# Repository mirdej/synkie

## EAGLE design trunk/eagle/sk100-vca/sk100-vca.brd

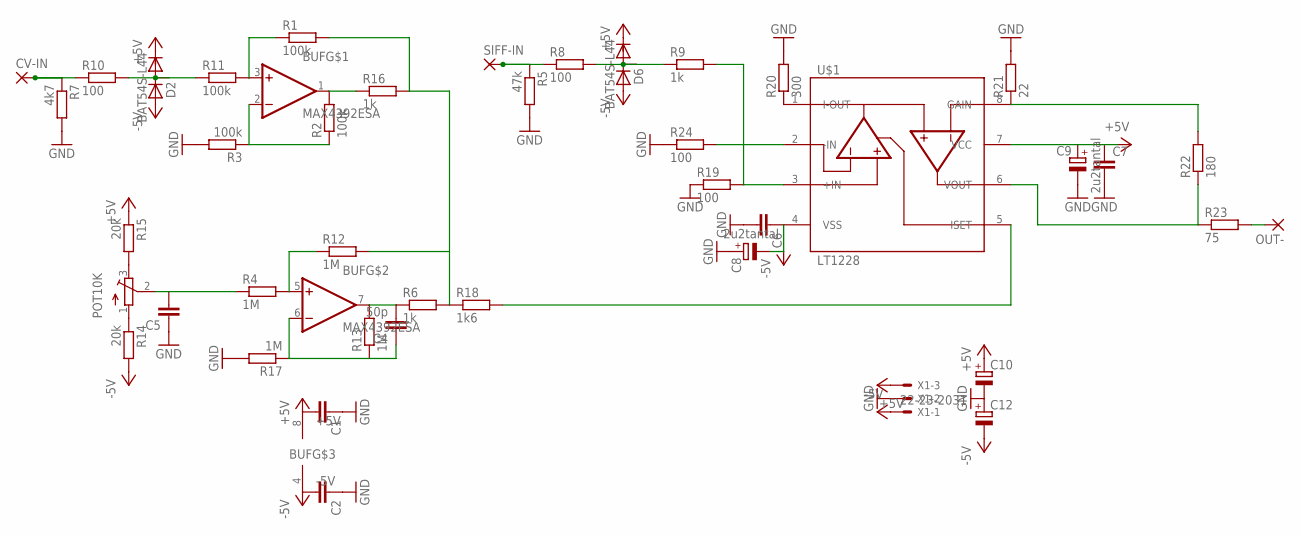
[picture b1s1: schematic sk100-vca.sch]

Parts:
BUF: MAX4392ESA; SO08
C1, C2, C5, C6, C7: C-EUC1206; C1206
C4: 50p; C1206
C8, C9: 2u2tantal; CT6032
C10, C12: CPOL-EUCT6032; CT6032
CV-IN: 3,17/1,1
D2, D6: BAT54S-L44; SOT23
OUT-: 3,17/1,1
POT10K: 10k; ALPS_RK09K111_H
R1, R2, R3, R11: 100k; R1206
R4, R12, R13, R17: 1M; R1206
R5: 47k; R1206
R6, R9, R16: 1k; R1206
R7: 4k7; R1206
R8, R10, R19, R24: 100; R1206
R14, R15: 20k; R1206
R18: 1k6; R1206
R20: 300; R1206
R21: 22; R1206
R22: 180; R1206
R23: 75; R1206
SIFF-IN: 3,17/1,1
U$1: LT1228; SO08
X1: 22-23-2031

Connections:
+5V: BUF.8 (+5V), C1.2, C7.1, C9.+, C10.+, D2.2 (C), D6.2 (C), R15.1, U$1.7 (VCC), X1.3
-5V: BUF.4 (-5V), C2.2, C6.1, C8.-, C12.-, D2.1 (A), D6.1 (A), R14.2, U$1.4 (VSS), X1.1
GND: C1.1, C2.1, C5.1, C6.2, C7.2, C8.+, C9.-, C10.-, C12.+, R3.2, R5.2, R7.2, R17.2, R19.1, R20.2, R21.2, R24.1, X1.2
unnamed: C5.2, POT10K.2 (W), R4.1
unnamed: POT10K.1 (S), R14.1
unnamed: POT10K.3 (E), R15.2
unnamed: BUF.2 (-IN), R2.1, R3.1
unnamed: R9.2, R19.2, U$1.3 (+IN)
unnamed: R20.1, U$1.1 (I-OUT)
unnamed: BUF.5 (+IN), R4.2, R12.1
unnamed: BUF.7 (OUT), C4.2, R6.1, R13.2
unnamed: R21.1, R22.2, U$1.8 (GAIN)
unnamed: CV-IN.1, R7.1, R10.1
unnamed: D2.3 (AC), R10.2, R11.1
unnamed: BUF.6 (-IN), C4.1, R13.1, R17.1
unnamed: BUF.3 (+IN), R1.1, R11.2
unnamed: R5.1, R8.1, SIFF-IN.1
unnamed: D6.3 (AC), R8.2, R9.1
unnamed: BUF.1 (OUT), R2.2, R16.1
unnamed: R18.2, U$1.5 (ISET)
unnamed: R1.2, R6.2, R12.2, R16.2, R18.1
unnamed: R22.1, R23.1, U$1.6 (VOUT)
unnamed: OUT-.1, R23.2
unnamed: R24.2, U$1.2 (-IN)

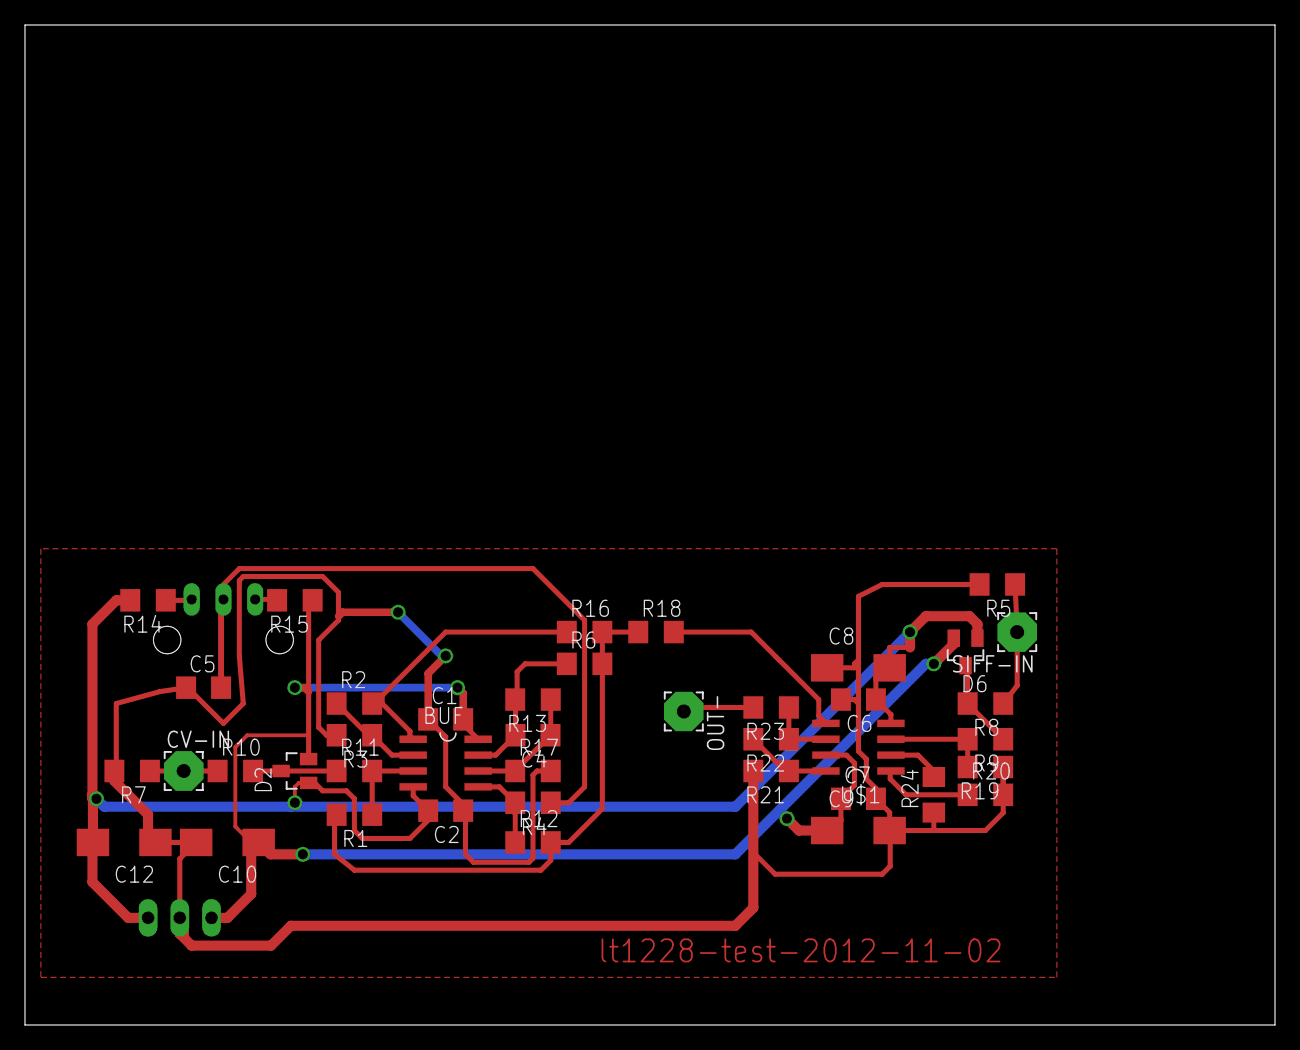
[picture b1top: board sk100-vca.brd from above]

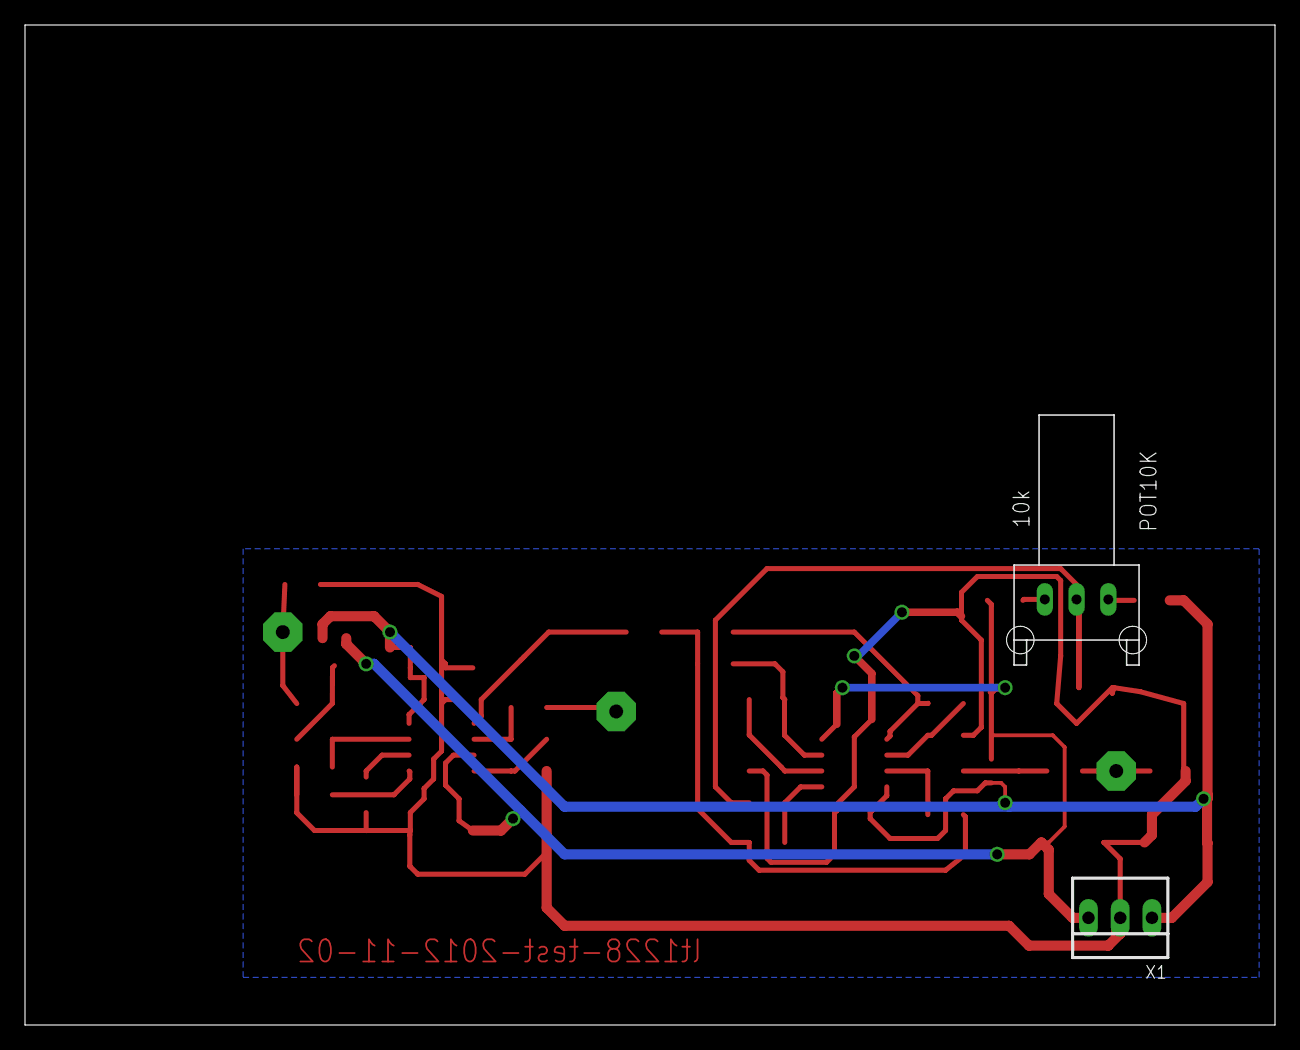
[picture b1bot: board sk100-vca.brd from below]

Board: 2 copper layers, 100.0 x 80.0 mm, 43 parts (2 on the bottom side), 24 nets.

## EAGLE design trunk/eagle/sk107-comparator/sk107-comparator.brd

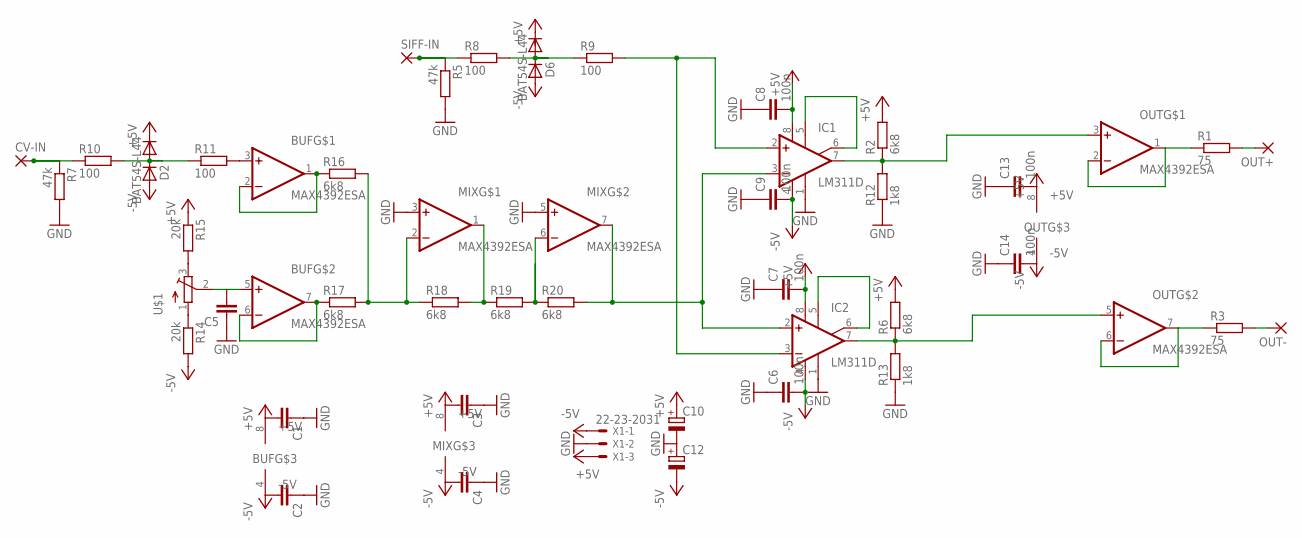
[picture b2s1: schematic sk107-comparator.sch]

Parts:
BUF: MAX4392ESA; SO08
C1, C2, C3, C4, C5: C-EUC1206; C1206
C6, C7, C8, C9, C13, C14: 100n; C0805
C10, C12: CPOL-EUE2.5-7; E2,5-7
CV-IN: 3,17/1,1
D2, D6: BAT54S-L44; SOT23
IC1, IC2: LM311D; SO08
MIX: MAX4392ESA; SO08
OUT: MAX4392ESA; SO08
OUT+: 3,17/1,1
OUT-: 3,17/1,1
R1, R3: 75; R1206
R2, R6, R16, R17, R18, R19, R20: 6k8; R1206
R5, R7: 47k; R1206
R8, R9, R10, R11: 100; R1206
R12, R13: 1k8; R1206
R14, R15: 20k; R1206
SIFF-IN: 3,17/1,1
U$1: ALPS_RK09K111_H09L1120; ALPS_RK09L1120
X1: 22-23-2031

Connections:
+5V: BUF.8 (+5V), C1.2, C3.2, C7.2, C8.2, C10.+, C13.2, D2.2 (C), D6.2 (C), IC1.8 (V+), IC2.8 (V+), MIX.8 (+5V), OUT.8 (+5V), R2.2, R6.2, R15.1, X1.3
-5V: BUF.4 (-5V), C2.2, C4.2, C6.2, C9.2, C12.-, C14.2, D2.1 (A), D6.1 (A), IC1.4 (V-), IC2.4 (V-), MIX.4 (-5V), OUT.4 (-5V), R14.2, X1.1
GND: C1.1, C2.1, C3.1, C4.1, C5.1, C6.1, C7.1, C8.1, C9.1, C10.-, C12.+, C13.1, C14.1, IC1.1 (GND), IC2.1 (GND), MIX.3 (+IN), MIX.5 (+IN), R5.2, R7.2, R12.1, R13.1, X1.2
unnamed: BUF.5 (+IN), C5.2, U$1.2 (W)
unnamed: R14.1, U$1.1 (S)
unnamed: R15.2, U$1.3 (E)
unnamed: OUT+.1, R1.2
unnamed: IC1.2 (+IN), IC2.3 (-IN), R9.2
unnamed: IC1.7 (OUT), OUT.3 (+IN), R2.1, R12.2
unnamed: IC1.5 (ON), IC1.6 (ON/STR)
unnamed: OUT.1 (OUT), OUT.2 (-IN), R1.1
unnamed: OUT-.1, R3.2
unnamed: CV-IN.1, R7.1, R10.1
unnamed: D2.3 (AC), R10.2, R11.1
unnamed: IC2.7 (OUT), OUT.5 (+IN), R6.1, R13.2
unnamed: BUF.6 (-IN), BUF.7 (OUT), R17.1
unnamed: BUF.3 (+IN), R11.2
unnamed: R5.1, R8.1, SIFF-IN.1
unnamed: D6.3 (AC), R8.2, R9.1
unnamed: BUF.1 (OUT), BUF.2 (-IN), R16.1
unnamed: IC2.5 (ON), IC2.6 (ON/STR)
unnamed: MIX.2 (-IN), R16.2, R17.2, R18.1
unnamed: MIX.1 (OUT), R18.2, R19.1
unnamed: MIX.6 (-IN), R19.2, R20.1
unnamed: IC1.3 (-IN), IC2.2 (+IN), MIX.7 (OUT), R20.2
unnamed: OUT.6 (-IN), OUT.7 (OUT), R3.1

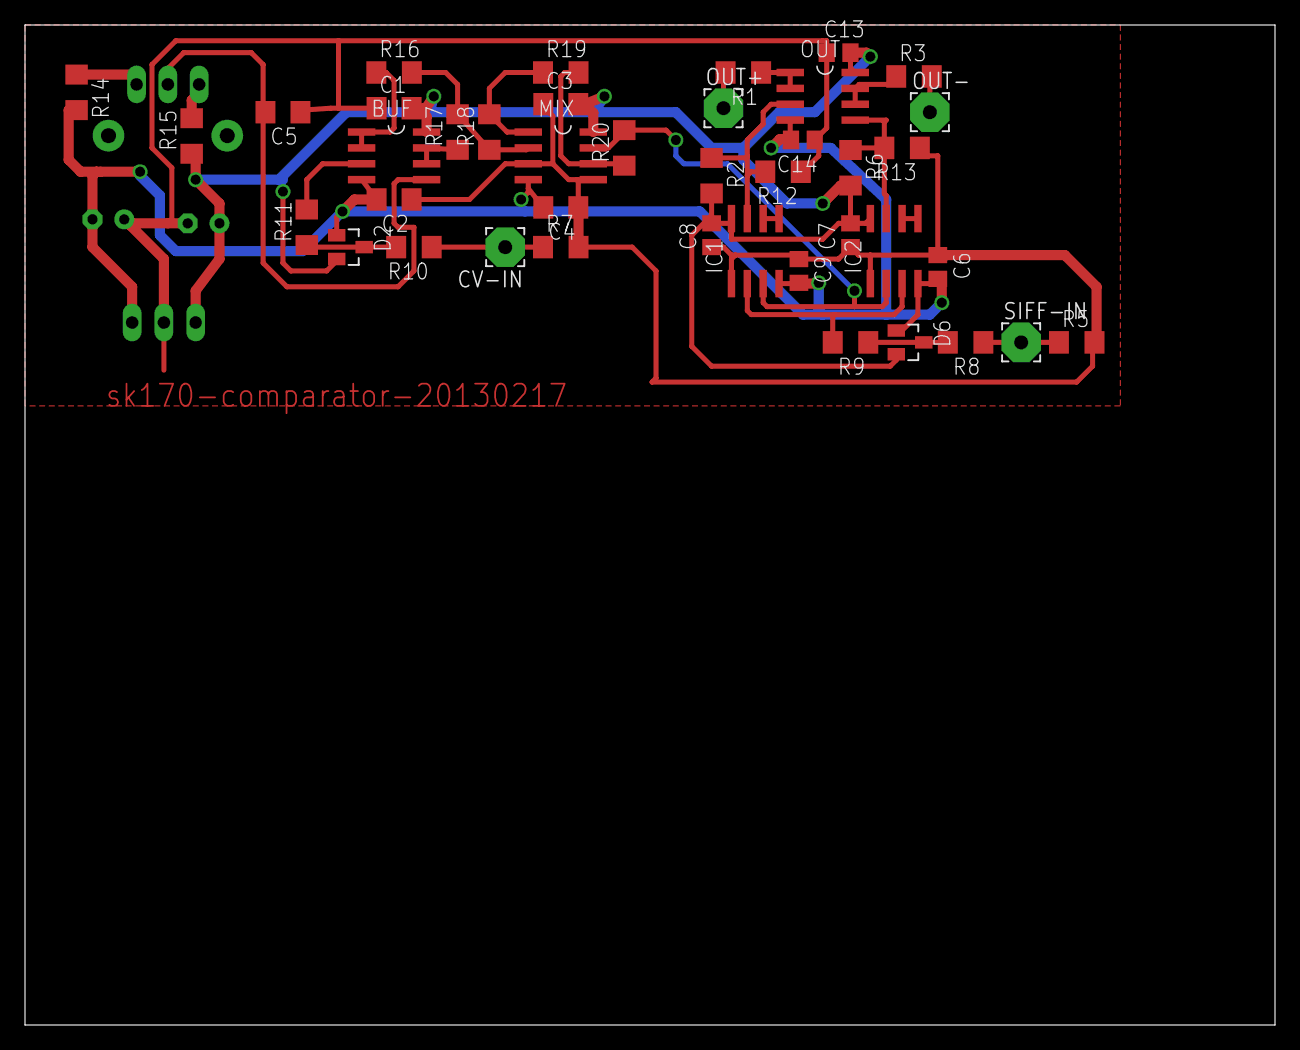
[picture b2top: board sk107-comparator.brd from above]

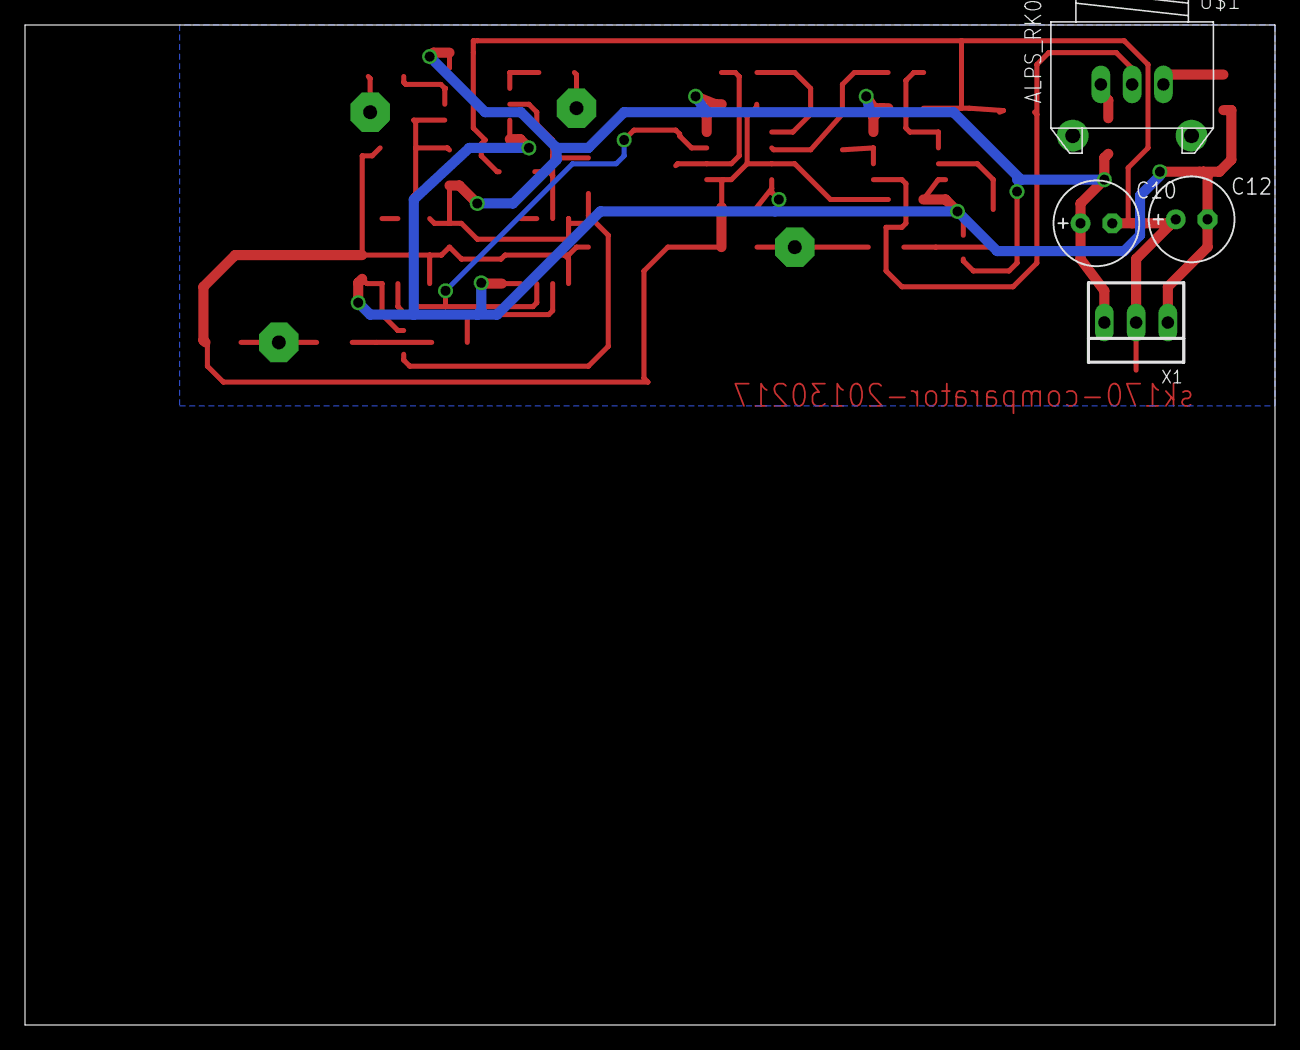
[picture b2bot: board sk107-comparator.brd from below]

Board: 2 copper layers, 100.0 x 80.0 mm, 45 parts (4 on the bottom side), 26 nets.

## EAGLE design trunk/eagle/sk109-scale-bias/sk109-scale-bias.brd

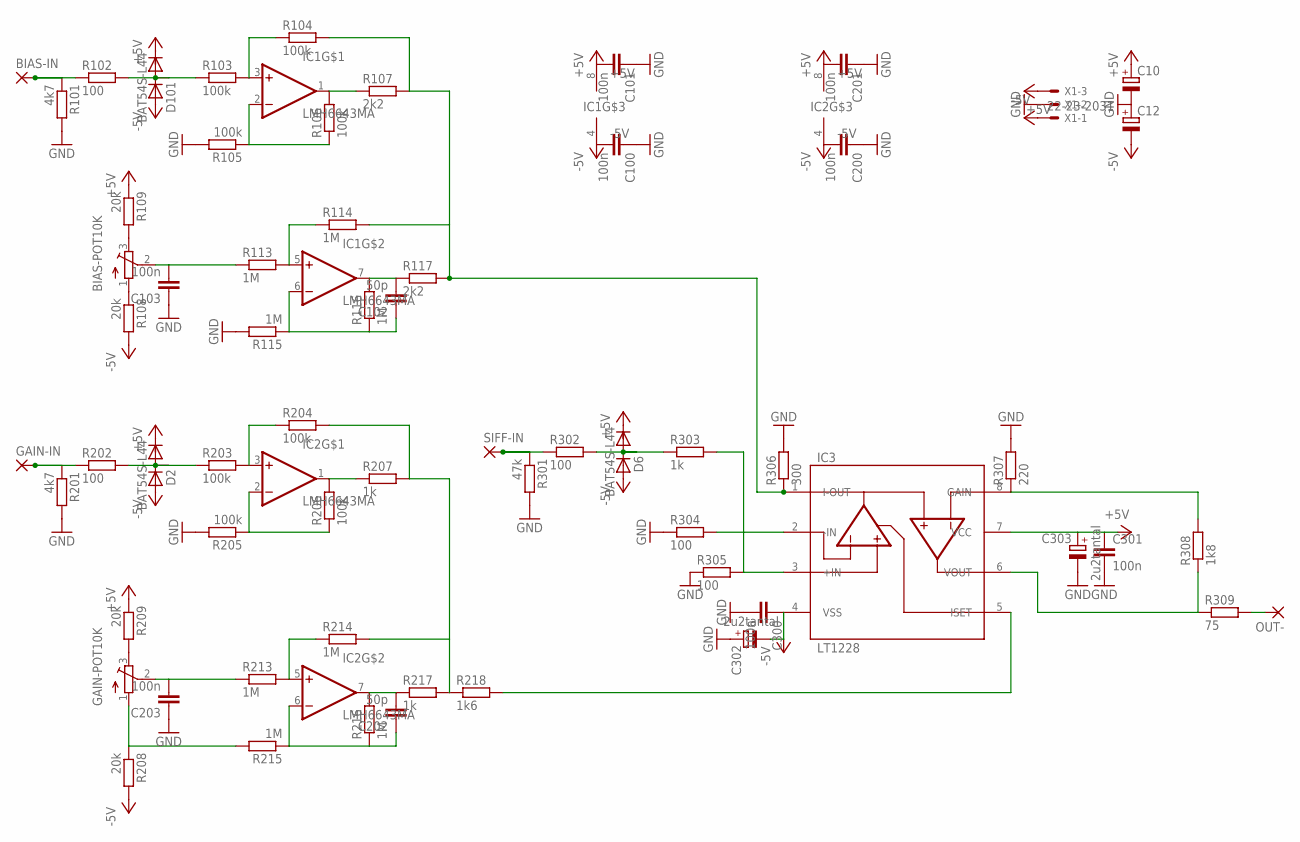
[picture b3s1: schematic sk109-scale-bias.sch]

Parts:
BIAS-IN: 3,17/1,1
BIAS-POT10K: 10k; ALPS_RK09L1120
C10, C12: CPOL-EUCT6032; CT6032
C100, C101, C103, C200, C201, C203, C300, C301: 100n; C1206
C102, C202: 50p; C1206
C302, C303: 2u2tantal; CT6032
D2, D6, D101: BAT54S-L44; SOT23
GAIN-IN: 3,17/1,1
GAIN-POT10K: 10k; ALPS_RK09L1120
IC1, IC2: LMH6643MA; SO08
IC3: LT1228; SO08
OUT-: 3,17/1,1
R101, R201: 4k7; R1206
R102, R202, R302, R304, R305: 100; R1206
R103, R104, R105, R106, R203, R204, R205, R206: 100k; R1206
R107, R117: 2k2; R1206
R108, R109, R208, R209: 20k; R1206
R113, R114, R115, R116, R213, R214, R215, R216: 1M; R1206
R207, R217, R303: 1k; R1206
R218: 1k6; R1206
R301: 47k; R1206
R306: 300; R1206
R307: 220; R1206
R308: 1k8; R1206
R309: 75; R1206
SIFF-IN: 3,17/1,1
X1: 22-23-2031

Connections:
+5V: C10.+, C101.2, C201.2, C301.1, C303.+, D2.2 (C), D6.2 (C), D101.2 (C), IC1.8 (+5V), IC2.8 (+5V), IC3.7 (VCC), R109.1, R209.1, X1.3
-5V: C12.-, C100.2, C200.2, C300.1, C302.-, D2.1 (A), D6.1 (A), D101.1 (A), IC1.4 (-5V), IC2.4 (-5V), IC3.4 (VSS), R108.2, R208.2, X1.1
D201: D2.3 (AC), R202.2, R203.1
D301: D6.3 (AC), R302.2, R303.1
GND: C10.-, C12.+, C100.1, C101.1, C103.1, C200.1, C201.1, C203.1, C300.2, C301.2, C302.+, C303.-, R101.2, R105.2, R115.2, R201.2, R205.2, R301.2, R304.1, R305.1, R306.2, R307.2, X1.2
unnamed: C203.2, GAIN-POT10K.2 (W), R213.1
unnamed: GAIN-POT10K.1 (S), R208.1, R215.2
unnamed: GAIN-POT10K.3 (E), R209.2
unnamed: IC2.2 (-IN), R205.1, R206.1
unnamed: IC3.3 (+IN), R303.2, R305.2
unnamed: IC3.1 (I-OUT), R104.2, R107.2, R114.2, R117.2, R306.1
unnamed: IC2.5 (+IN), R213.2, R214.1
unnamed: C202.2, IC2.7 (OUT), R216.2, R217.1
unnamed: IC3.8 (GAIN), R307.1, R308.2
unnamed: GAIN-IN.1, R201.1, R202.1
unnamed: C202.1, IC2.6 (-IN), R215.1, R216.1
unnamed: BIAS-IN.1, R101.1, R102.1
unnamed: IC2.3 (+IN), R203.2, R204.1
unnamed: R301.1, R302.1, SIFF-IN.1
unnamed: IC2.1 (OUT), R206.2, R207.1
unnamed: IC3.5 (ISET), R218.2
unnamed: R204.2, R207.2, R214.2, R217.2, R218.1
unnamed: IC3.6 (VOUT), R308.1, R309.1
unnamed: OUT-.1, R309.2
unnamed: IC3.2 (-IN), R304.2
unnamed: D101.3 (AC), R102.2, R103.1
unnamed: IC1.3 (+IN), R103.2, R104.1
unnamed: IC1.1 (OUT), R106.2, R107.1
unnamed: BIAS-POT10K.2 (W), C103.2, R113.1
unnamed: BIAS-POT10K.1 (S), R108.1
unnamed: BIAS-POT10K.3 (E), R109.2
unnamed: IC1.5 (+IN), R113.2, R114.1
unnamed: C102.2, IC1.7 (OUT), R116.2, R117.1
unnamed: C102.1, IC1.6 (-IN), R115.1, R116.1
R105: IC1.2 (-IN), R105.1, R106.1

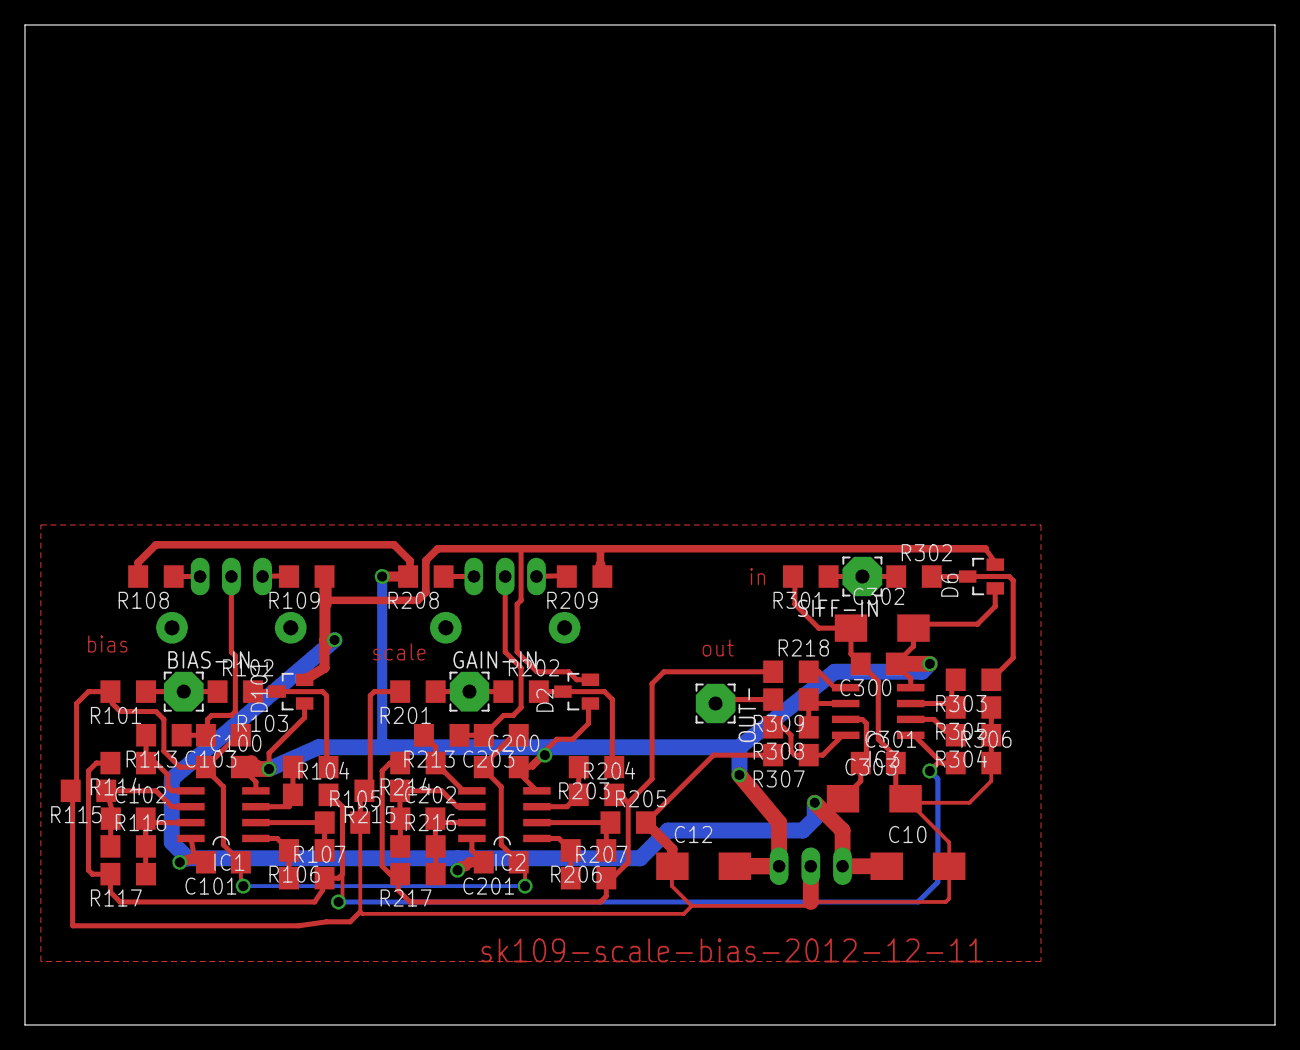
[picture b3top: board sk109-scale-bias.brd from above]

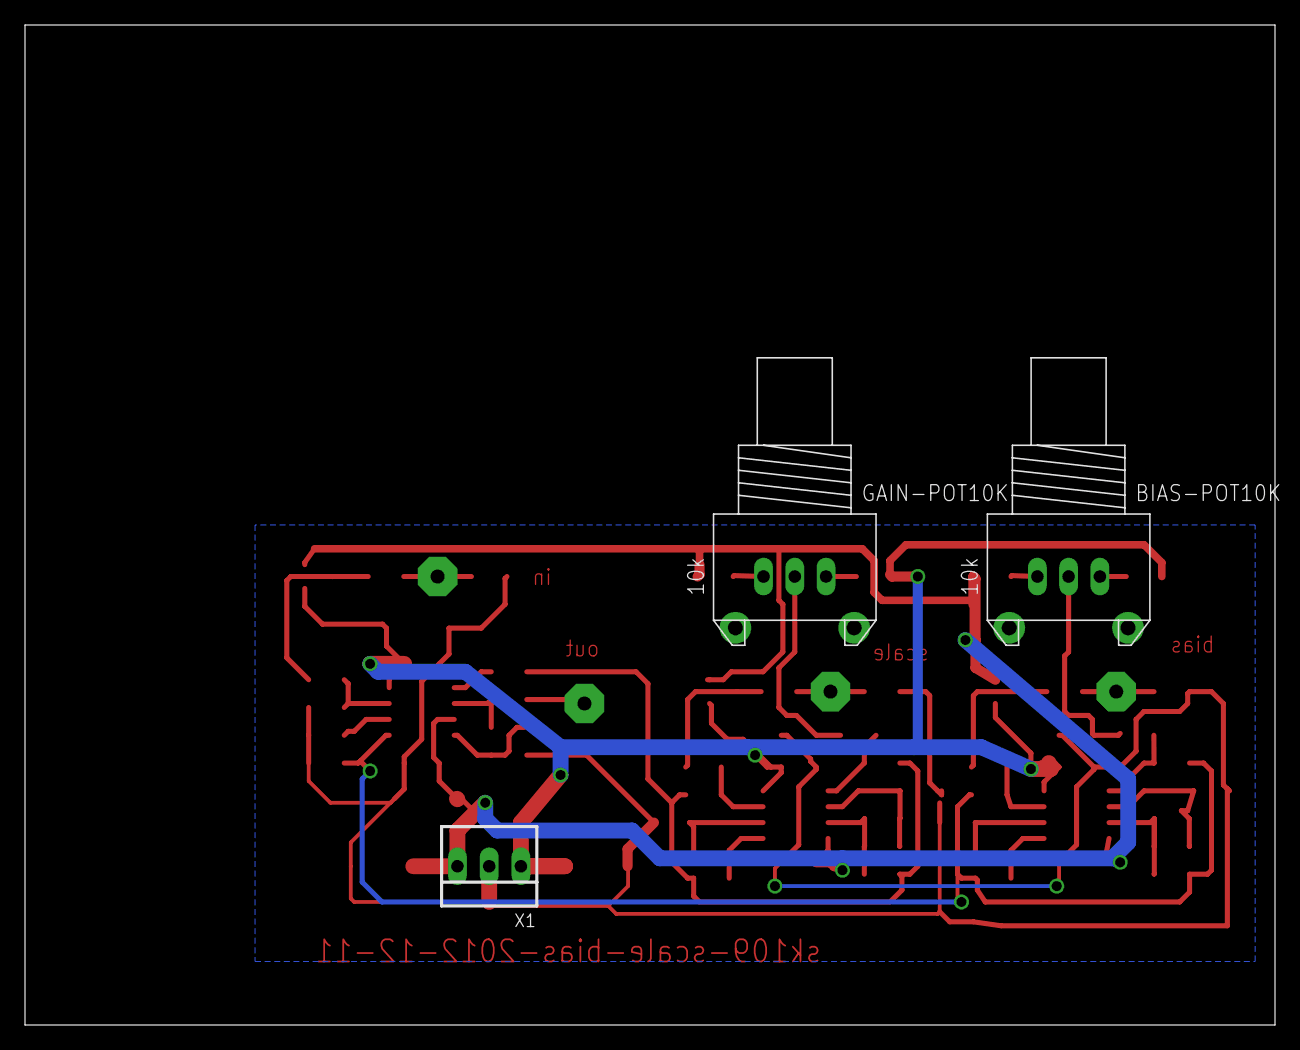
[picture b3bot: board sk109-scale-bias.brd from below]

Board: 2 copper layers, 100.0 x 80.0 mm, 65 parts (3 on the bottom side), 35 nets.

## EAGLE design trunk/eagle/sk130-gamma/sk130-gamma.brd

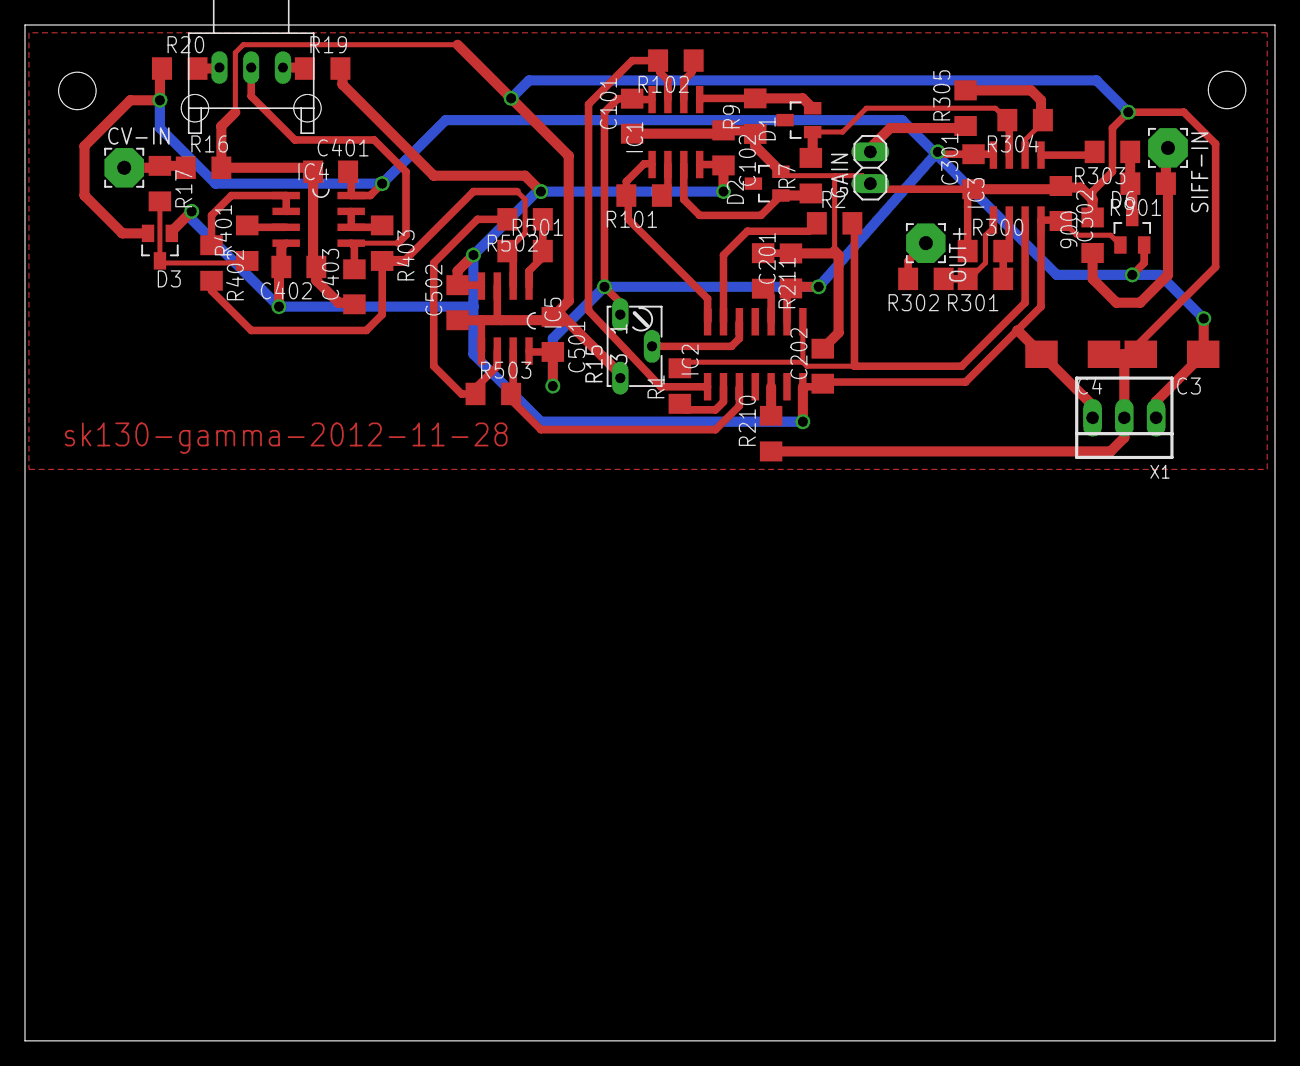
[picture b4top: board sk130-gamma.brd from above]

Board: 2 copper layers, 100.0 x 81.3 mm, 55 parts (0 on the bottom side), 36 nets.

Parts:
900: 4k7; R1206
C3, C4: CT6032
C101, C102, C201, C202, C301, C302, C403: 100n; C1206
C401, C402, C501, C502: C1206
CV-IN: 3,17/1,1
D1, D2, D3, D6: BAT54S-L44; SOT23
GAIN: 1X02
IC1, IC3: MAX4392; SO08
IC2: LT1251; SO14
IC4, IC5: MAX4392ESA; SO08
OUT+: 3,17/1,1
POT10K: 10k; ALPS_RK09K111_H
R1, R2: 1k5; R1206
R7, R9: 180; R1206
R15: B64W
R16: 47k; R1206
R17, R305, R401, R901: 100; R1206
R19, R20: 20k; R1206
R101, R102, R210, R211, R301, R303, R304: 1k; R1206
R300: inf; R1206
R302: 75; R1206
R402, R403, R501, R502, R503: 4k7; R1206
SIFF-IN: 3,17/1,1
X1: 22-23-2031

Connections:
+5V: C3.+, C101.2, C201.1, C301.2, C401.2, C501.2, D3.2, D6.2, IC1.8, IC2.9, IC3.8, IC4.8, IC5.8, R15.A, R20.1, X1.1
-5V: C4.-, C102.2, C202.1, C302.2, C402.2, C502.2, D3.1, D6.1, IC1.4, IC2.7, IC3.4, IC4.4, IC5.4, R19.2, X1.3
GND: 900.2, C3.-, C4.+, C101.1, C102.1, C201.2, C202.2, C301.1, C302.1, C401.1, C402.1, C403.1, C501.1, C502.1, D2.2, GAIN.1, IC5.3, IC5.5, R9.1, R15.E, R16.2, R210.1, R211.1, R300.1, X1.2
unnamed: IC3.6, R304.1, R305.2
unnamed: IC3.5, R303.2
unnamed: OUT+.1, R302.2
unnamed: IC2.8, IC3.3, R1.2, R2.2
unnamed: D1.1, IC3.7, R7.2, R304.2
unnamed: GAIN.2, R305.1
unnamed: IC3.2, R300.2, R301.1
unnamed: IC3.1, R301.2, R302.1
unnamed: IC2.5, R210.2
unnamed: D2.1, IC1.3, R7.1
unnamed: IC2.10, R211.2
unnamed: IC1.2, R101.1
unnamed: IC2.2, R1.1
unnamed: 900.1, R901.1, SIFF-IN.1
unnamed: D6.3, R303.1, R901.2
unnamed: IC1.6, R102.1
unnamed: IC1.1, IC2.14, R101.2
unnamed: IC2.12, R15.S
unnamed: CV-IN.1, R16.1, R17.1
unnamed: D3.3, R17.2, R401.1
unnamed: IC4.3, R401.2
unnamed: IC4.1, IC4.2, R402.1
unnamed: IC4.6, IC4.7, R403.1
unnamed: IC5.2, R402.2, R403.2, R501.1
unnamed: IC5.1, R501.2, R502.1
unnamed: IC5.6, R502.2, R503.1
unnamed: IC2.3, IC5.7, R503.2
unnamed: C403.2, IC4.5, POT10K.2
unnamed: POT10K.1, R19.1
unnamed: POT10K.3, R20.2
unnamed: IC1.7, IC2.1, R102.2
unnamed: IC2.13, R2.1
unnamed: D1.2, IC1.5, R9.2
